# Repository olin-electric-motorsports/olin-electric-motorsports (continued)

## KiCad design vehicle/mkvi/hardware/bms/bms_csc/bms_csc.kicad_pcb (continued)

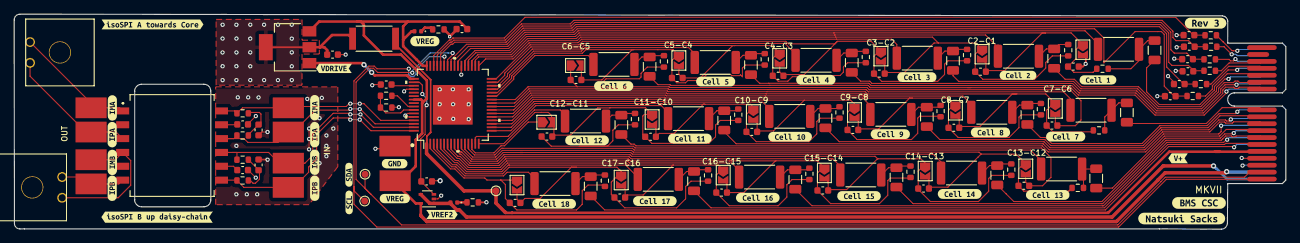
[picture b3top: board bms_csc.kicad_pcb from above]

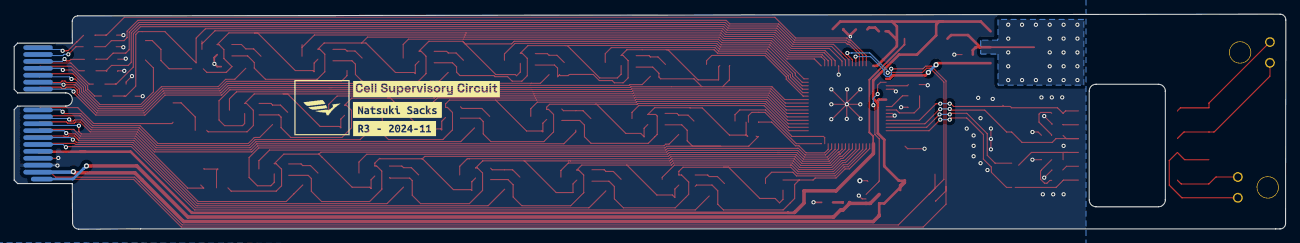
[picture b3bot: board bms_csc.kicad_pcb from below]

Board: 2 copper layers, 183.7 x 31.1 mm, 183 parts (3 on the bottom side), 110 nets.

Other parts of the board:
kibuzzard-63B4D82F: G***; kibuzzard-63B4D82F
kibuzzard-63B4D834: G***; kibuzzard-63B4D834
kibuzzard-63B4E58E: G***; kibuzzard-63B4E58E
kibuzzard-63B4E59A: G***; kibuzzard-63B4E59A
kibuzzard-63B4E581: G***; kibuzzard-63B4E581
kibuzzard-63B4E593: G***; kibuzzard-63B4E593
kibuzzard-63B4EB9B: G***; kibuzzard-63B4EB9B
kibuzzard-63B4EBA9, kibuzzard-63B4EBA9#2: G***; kibuzzard-63B4EBA9
kibuzzard-63B4EBAD, kibuzzard-63B4EBAD#2: G***; kibuzzard-63B4EBAD
kibuzzard-63B4EBB3, kibuzzard-63B4EBB3#2: G***; kibuzzard-63B4EBB3
kibuzzard-63B4EBB8, kibuzzard-63B4EBB8#2: G***; kibuzzard-63B4EBB8
kibuzzard-63B4EBF9: G***; kibuzzard-63B4EBF9
kibuzzard-63B4EC1B: G***; kibuzzard-63B4EC1B
kibuzzard-63B4EC4E: G***; kibuzzard-63B4EC4E
kibuzzard-63B4EC5B: G***; kibuzzard-63B4EC5B
kibuzzard-63B4EC6B: G***; kibuzzard-63B4EC6B
kibuzzard-63B4EC7A: G***; kibuzzard-63B4EC7A
kibuzzard-63B4EC20: G***; kibuzzard-63B4EC20
kibuzzard-63B4EC53: G***; kibuzzard-63B4EC53
kibuzzard-63B4EC66: G***; kibuzzard-63B4EC66
kibuzzard-63B4EC74: G***; kibuzzard-63B4EC74
kibuzzard-63B4EC80: G***; kibuzzard-63B4EC80
kibuzzard-63B4ED2A: G***; kibuzzard-63B4ED2A
kibuzzard-63B4ED25: G***; kibuzzard-63B4ED25
kibuzzard-63B4ED94: G***; kibuzzard-63B4ED94
kibuzzard-63B8E034: G***; kibuzzard-63B8E034
kibuzzard-63B8E079: G***; kibuzzard-63B8E079
kibuzzard-63BF4CDF: G***; kibuzzard-63BF4CDF
kibuzzard-63BF4D5E: G***; kibuzzard-63BF4D5E
kibuzzard-63BF5C8C: G***; kibuzzard-63BF5C8C
kibuzzard-672FC8C8: G***; kibuzzard-672FC8C8
kibuzzard-672FC89C: G***; kibuzzard-672FC89C
kibuzzard-672FCAF7: G***; kibuzzard-672FCAF7
kibuzzard-672FCF9D: G***; kibuzzard-672FCF9D
kibuzzard-672FD13B: G***; kibuzzard-672FD13B
kibuzzard-672FD17B: G***; kibuzzard-672FD17B
kibuzzard-673125E9: G***; kibuzzard-673125E9
kibuzzard-6731260F: G***; kibuzzard-6731260F

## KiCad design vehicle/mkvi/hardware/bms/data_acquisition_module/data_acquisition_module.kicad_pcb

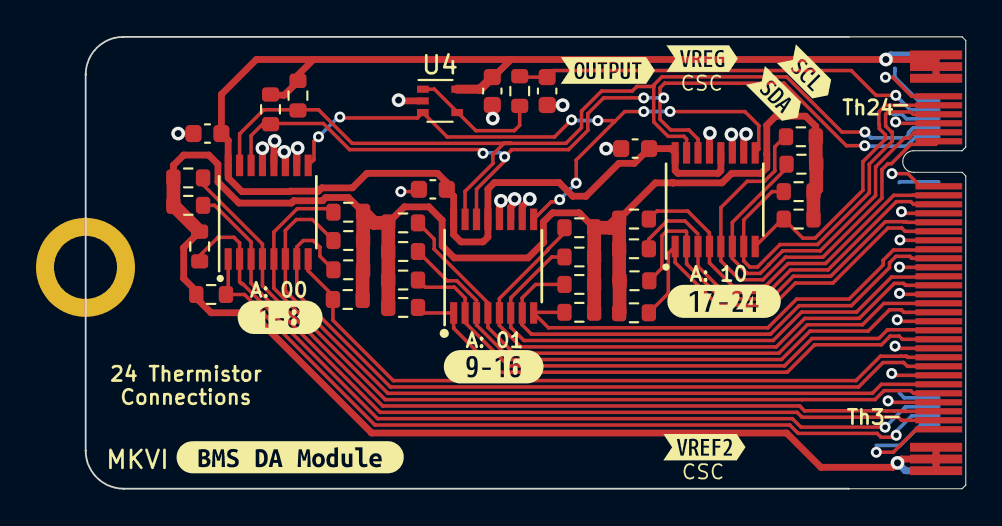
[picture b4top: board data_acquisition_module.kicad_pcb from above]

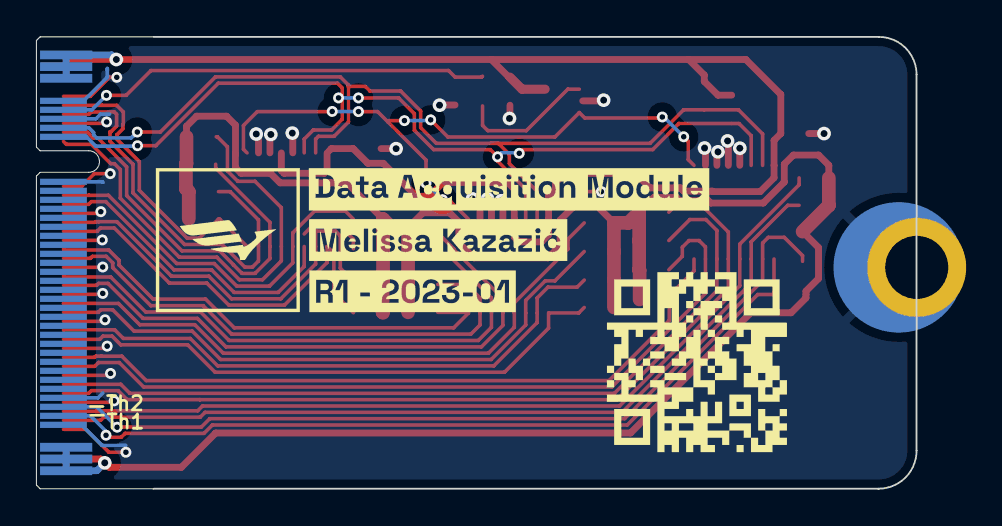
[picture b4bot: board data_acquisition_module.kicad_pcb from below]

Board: 2 copper layers, 48.9 x 25.1 mm, 51 parts (4 on the bottom side), 32 nets.

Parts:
C1, C2, C4: C_1uF; C_0603
C3: C_10nF; C_0603
C5: C_0.1uF; C_0603
H1: M.2_MountingHole; M.2_Mount
J1: Automotive_M.2_Edge_Connector
QR*****: hw.oem.to/6_BMS-DA_1; QR_6_BMS-DA_1
R1, R2, R3, R4, R5, R6, R7, R8, R9, R10, R11, R12, R13, R14, R15, R16, R17, R18, R19, R20, R21, R22, R23, R24: R_100K; R_0603
R25: R_100; R_0603
R26, R27: 15KR_DNP; R_0603
U1, U2, U3: LTC1380IGN; SSOP-16_3.9x4.9mm_P0.635mm
U4: MCP6001T-I-LT; SOT-353_SC-70-5
kibuzzard-63A54BB0: G***; kibuzzard-63A54BB0
kibuzzard-63A54BCB: G***; kibuzzard-63A54BCB
kibuzzard-63A54BE3: G***; kibuzzard-63A54BE3
kibuzzard-63BF51CA: G***; kibuzzard-63BF51CA
kibuzzard-63BF55B8: G***; kibuzzard-63BF55B8
kibuzzard-63BF55D1: G***; kibuzzard-63BF55D1
kibuzzard-63BF465A: G***; kibuzzard-63BF465A
kibuzzard-63BF547A: G***; kibuzzard-63BF547A
kibuzzard-63BF4696: G***; kibuzzard-63BF4696
kibuzzard-63BF5052: G***; kibuzzard-63BF5052
kibuzzard-63BF5430: G***; kibuzzard-63BF5430
kibuzzard-63BF5451: G***; kibuzzard-63BF5451

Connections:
/MUX_GROUP_OUTPUT: C3.1, J1.42, R25.1
/SCL: J1.44, R26.1, U1.15 (SCL), U2.15 (SCL), U3.15 (SCL)
/SDA: J1.45, R27.1, U1.14 (SDA), U2.14 (SDA), U3.14 (SDA)
/THERM_1: J1.72, R1.2, U1.1 (S0)
/THERM_2: J1.71, R2.2, U1.2 (S1)
/THERM_3: J1.36, R3.2, U1.3 (S2)
/THERM_4: J1.35, R4.2, U1.4 (S3)
/THERM_5: J1.33, R5.2, U1.5 (S4)
/THERM_6: J1.32, R6.2, U1.6 (S5)
/THERM_7: J1.30, R7.2, U1.7 (S6)
/THERM_8: J1.29, R8.2, U1.8 (S7)
/THERM_9: J1.27, R9.2, U2.1 (S0)
/THERM_10: J1.26, R10.2, U2.2 (S1)
/THERM_11: J1.24, R11.2, U2.3 (S2)
/THERM_12: J1.23, R12.2, U2.4 (S3)
/THERM_13: J1.21, R13.2, U2.5 (S4)
/THERM_14: J1.20, R14.2, U2.6 (S5)
/THERM_15: J1.18, R15.2, U2.7 (S6)
/THERM_16: J1.17, R16.2, U2.8 (S7)
/THERM_17: J1.15, R17.2, U3.1 (S0)
/THERM_18: J1.14, R18.2, U3.2 (S1)
/THERM_19: J1.12, R19.2, U3.3 (S2)
/THERM_20: J1.11, R20.2, U3.4 (S3)
/THERM_21: J1.9, R21.2, U3.5 (S4)
/THERM_22: J1.8, R22.2, U3.6 (S5)
/THERM_23: J1.6, R23.2, U3.7 (S6)
/THERM_24: J1.5, R24.2, U3.8 (S7)
/VREF2: J1.P38, J1.P39, J1.P40, R1.1, R2.1, R3.1, R4.1, R5.1, R6.1, R7.1, R8.1, R9.1, R10.1, R11.1, R12.1, R13.1, R14.1, R15.1, R16.1, R17.1, R18.1, R19.1, R20.1, R21.1, R22.1, R23.1, R24.1
/VREG: C1.1, C2.1, C4.1, C5.1, J1.P1, J1.P2, J1.P3, R26.2, R27.2, U1.16 (VCC), U2.13 (A0), U2.16 (VCC), U3.12 (A1), U3.16 (VCC), U4.5 (V+)
GND: C1.2, C2.2, C3.2, C4.2, C5.2, H1.1, J1.4, J1.7, J1.10, J1.13, J1.16, J1.19, J1.22, J1.25, J1.28, J1.31, J1.34, J1.37, J1.41, J1.43, J1.46, J1.70, J1.73, U1.10 (VEE), U1.11 (GND), U1.12 (A1), U1.13 (A0), U2.10 (VEE), U2.11 (GND), U2.12 (A1), U3.10 (VEE), U3.11 (GND), U3.13 (A0), U4.2 (V-)
unnamed: R25.2, U4.1, U4.4 (-)
unnamed: U1.9 (D0), U2.9 (D0), U3.9 (D0), U4.3 (+)
